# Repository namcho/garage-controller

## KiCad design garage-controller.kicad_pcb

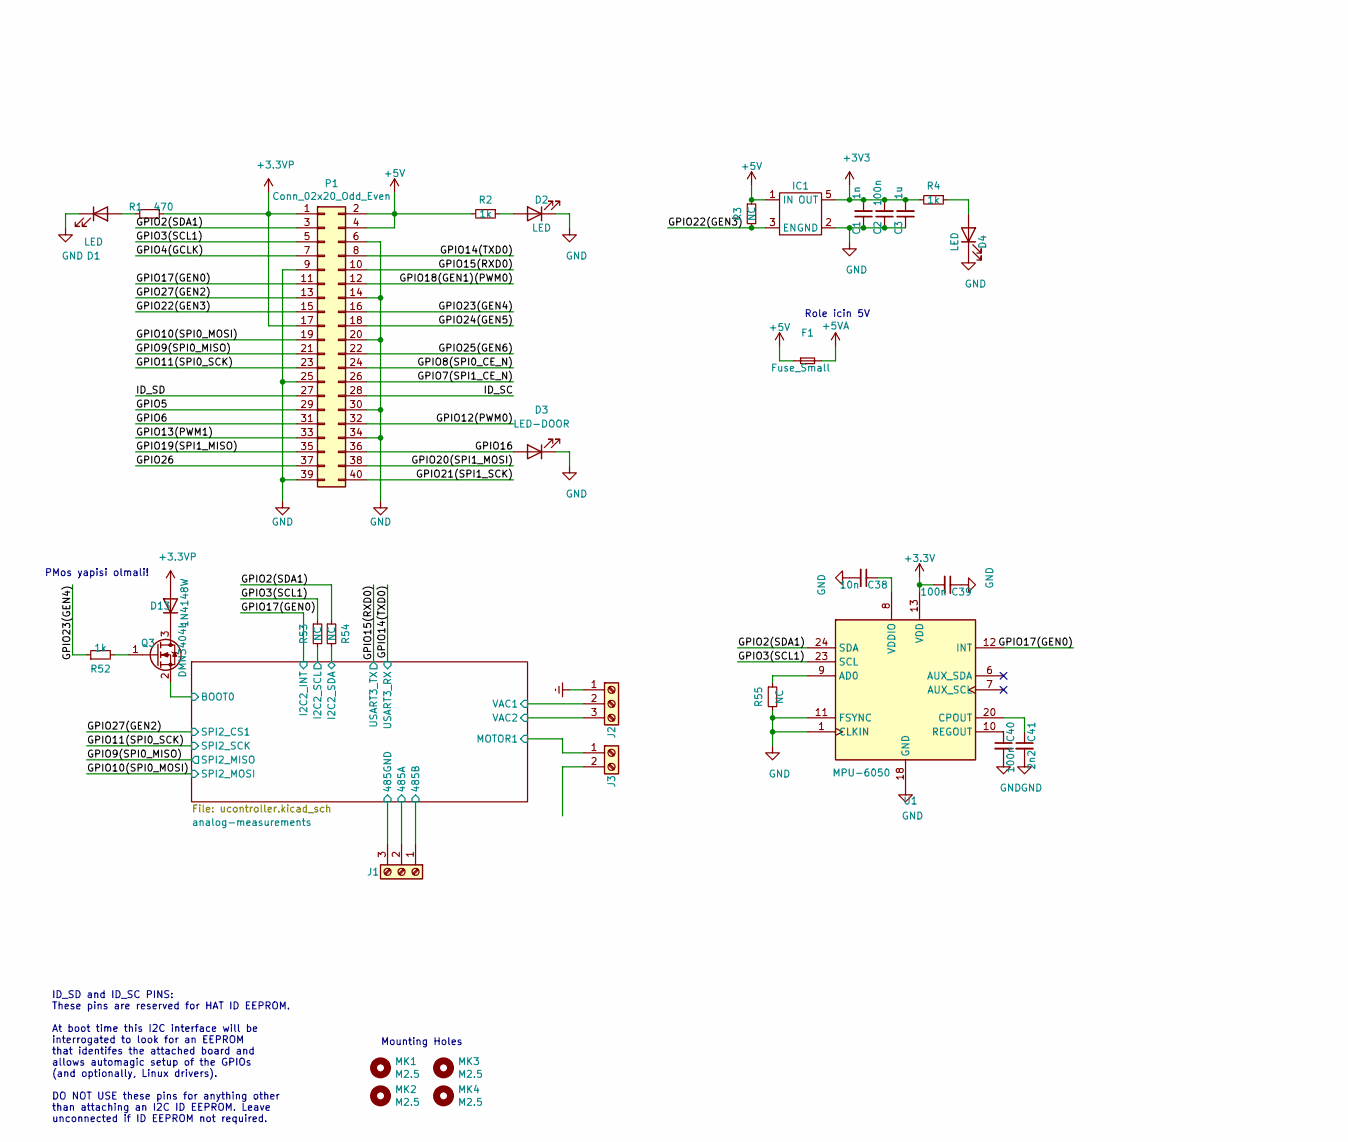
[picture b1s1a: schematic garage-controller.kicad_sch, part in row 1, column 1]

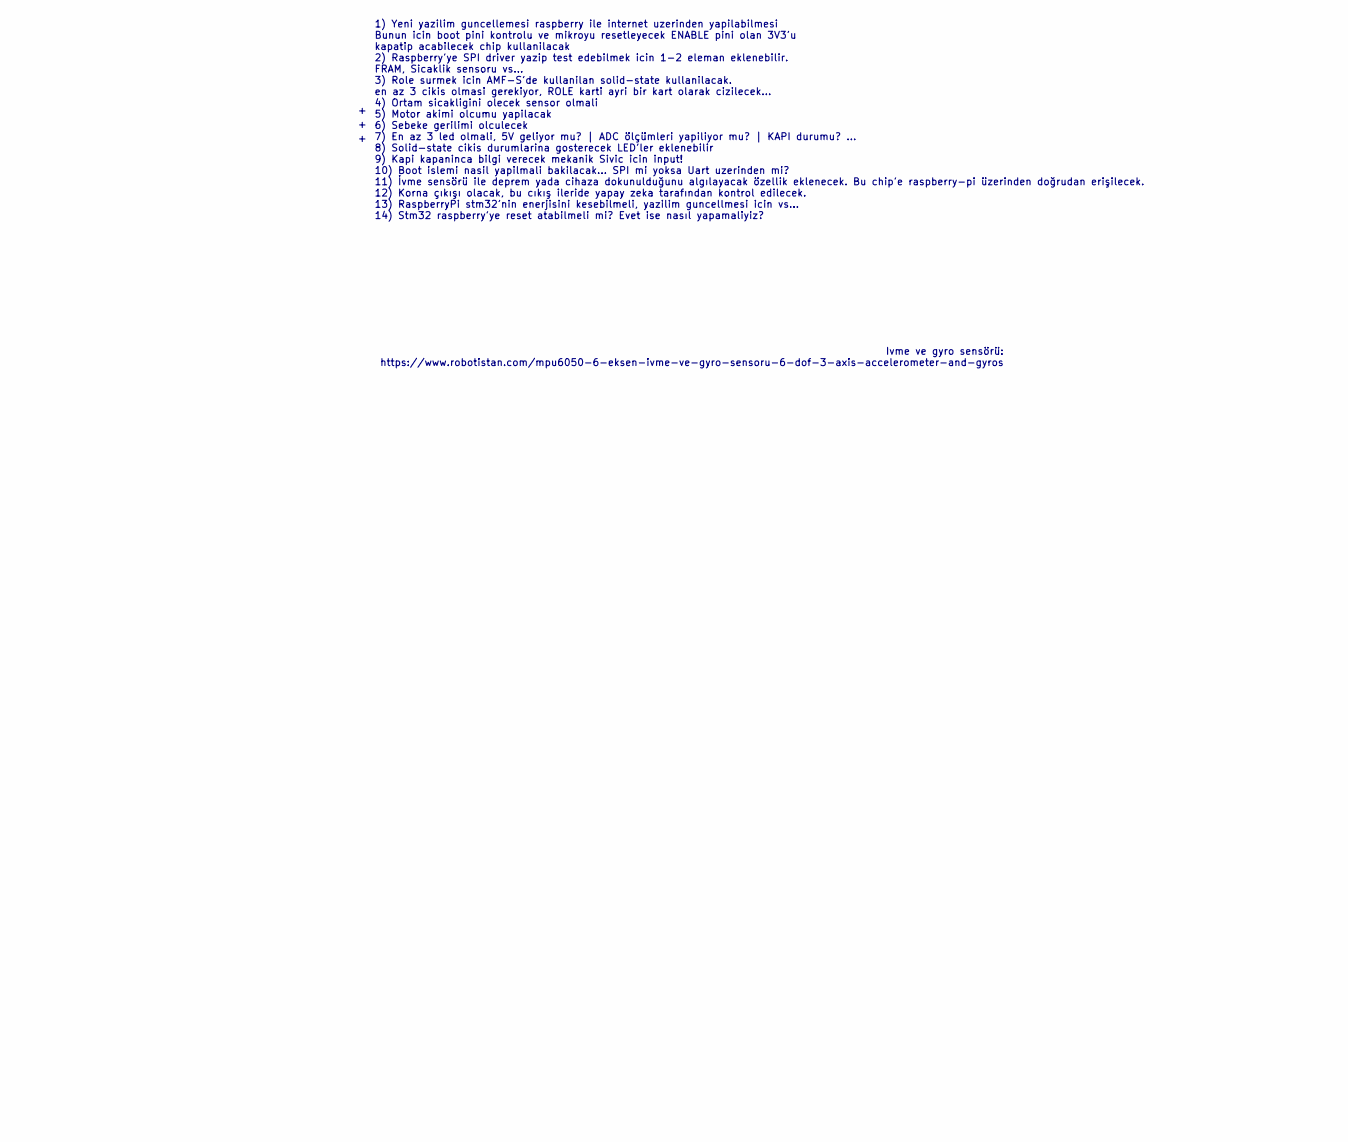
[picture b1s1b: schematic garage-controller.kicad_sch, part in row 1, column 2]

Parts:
C1: 1n; C_0603_1608Metric
C2, C39, C40: 100n; C_0603_1608Metric
C3: 1u; C_0603_1608Metric
C38: 10n; C_0603_1608Metric
C41: 2n2; C_0603_1608Metric
D1, D2, D4: LED; LED_0805_2012Metric
D3: LED-DOOR; LED_0805_2012Metric
D13: 1N4148W; D_SOD-123
F1: Fuse_Small; Fuse_1206_3216Metric
IC1: NCP115ASN330T2G; TSOP-5_1.65x3.05mm_P0.95mm
J1: Screw_Terminal_01x03; PhoenixContact_MCV_1,5_3-G-3.81_1x03_P3.81mm_Vertical
J2: Screw_Terminal_01x03; PhoenixContact_MCV_1,5_3-G-5.08_1x03_P5.08mm_Vertical
J3: Screw_Terminal_01x02; PhoenixContact_MCV_1,5_2-G-5.08_1x02_P5.08mm_Vertical
MK1, MK2, MK3, MK4: M2.5; MountingHole_2.7mm_M2.5
P1: Conn_02x20_Odd_Even; PinSocket_2x20_P2.54mm_Vertical
Q3: DMN3404L; SOT-23
R1: 470; R_0603_1608Metric
R2, R4, R52: 1k; R_0603_1608Metric
R3, R53, R54, R55: NC; R_0603_1608Metric
U1: MPU-6050; InvenSense_QFN-24_4x4mm_P0.5mm

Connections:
+3.3VP: D13.2 (A), P1.1, P1.17, R1.1
+5V: F1.1, IC1.1 (IN), P1.2, P1.4, R2.2, R3.1; also elsewhere on the board
+5VA: F1.2; also elsewhere on the board
/GPIO2(SDA1): P1.3, R54.1, U1.24 (SDA)
/GPIO3(SCL1): P1.5, R53.1, U1.23 (SCL)
/GPIO4(GCLK): P1.7
/GPIO5: P1.29
/GPIO6: P1.31
/GPIO7(SPI1_CE_N): P1.26
/GPIO8(SPI0_CE_N): P1.24
/GPIO9(SPI0_MISO): P1.21; also elsewhere on the board
/GPIO10(SPI0_MOSI): P1.19; also elsewhere on the board
/GPIO11(SPI0_SCK): P1.23; also elsewhere on the board
/GPIO12(PWM0): P1.32
/GPIO13(PWM1): P1.33
/GPIO14(TXD0): P1.8; also elsewhere on the board
/GPIO15(RXD0): P1.10; also elsewhere on the board
/GPIO16: D3.2 (A), P1.36
/GPIO17(GEN0): P1.11, U1.12 (INT); also elsewhere on the board
/GPIO18(GEN1)(PWM0): P1.12
/GPIO19(SPI1_MISO): P1.35
/GPIO20(SPI1_MOSI): P1.38
/GPIO21(SPI1_SCK): P1.40
/GPIO22(GEN3): IC1.3 (EN), P1.15, R3.2
/GPIO23(GEN4): P1.16, R52.1
/GPIO24(GEN5): P1.18
/GPIO25(GEN6): P1.22
/GPIO26: P1.37
/GPIO27(GEN2): P1.13; also elsewhere on the board
/ID_SC: P1.28
/ID_SD: P1.27
/analog-measurements/485A: J1.2; also elsewhere on the board
/analog-measurements/485B: J1.1; also elsewhere on the board
/analog-measurements/485GND: J1.3; also elsewhere on the board
/analog-measurements/BOOT0: Q3.2 (S); also elsewhere on the board
/analog-measurements/I2C2_SCL: R53.2; also elsewhere on the board
/analog-measurements/I2C2_SDA: R54.2; also elsewhere on the board
/analog-measurements/MOTOR1: J3.1; also elsewhere on the board
/analog-measurements/VAC1: J2.2; also elsewhere on the board
/analog-measurements/VAC2: J2.3; also elsewhere on the board
Earth: J2.1; also elsewhere on the board
GND: C1.1, C2.1, C3.1, C38.2, C39.1, C40.2, C41.2, D1.1 (K), D2.1 (K), D3.1 (K), D4.1 (K), IC1.2 (GND), P1.6, P1.9, P1.14, P1.20, P1.25, P1.30, P1.34, P1.39, R55.2, U1.1 (CLKIN), U1.11 (FSYNC), U1.18 (GND); also elsewhere on the board
unnamed: C38.1, U1.8 (VDDIO)
unnamed: C40.1, U1.10 (REGOUT)
unnamed: C41.1, U1.20 (CPOUT)
unnamed: D1.2 (A), R1.2
unnamed: D2.2 (A), R2.1
unnamed: D4.2 (A), R4.1
unnamed: D13.1 (K), Q3.3 (D)
unnamed: Q3.1 (G), R52.2
unnamed: R55.1, U1.9 (AD0)

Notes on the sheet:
ID_SD and ID_SC PINS: These pins are reserved for HAT ID EEPROM. At boot time this I2C interface will be interrogated to look for an EEPROM that identifes the attached board and allows automagic setup of the GPIOs (and optionally, Linux drivers). DO NOT USE these pins for anything other than attach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
PMos yapisi olmali!
Mounting Holes
Role icin 5V
1) Yeni yazilim guncellemesi raspberry ile internet uzerinden yapilabilmesi Bunun icin boot pini kontrolu ve mikroyu resetleyecek ENABLE pini olan 3V3'u kapatip acabilecek chip kullanilacak 2) Raspberry'ye SPI driver yazip test edebilmek icin 1-2 eleman eklenebilir. FRAM, Sicaklik sensoru vs... 3) 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
Ivme ve gyro sensörü: https://www.robotistan.com/mpu6050-6-eksen-ivme-ve-gyro-sensoru-6-dof-3-axis-accelerometer-and-gyros

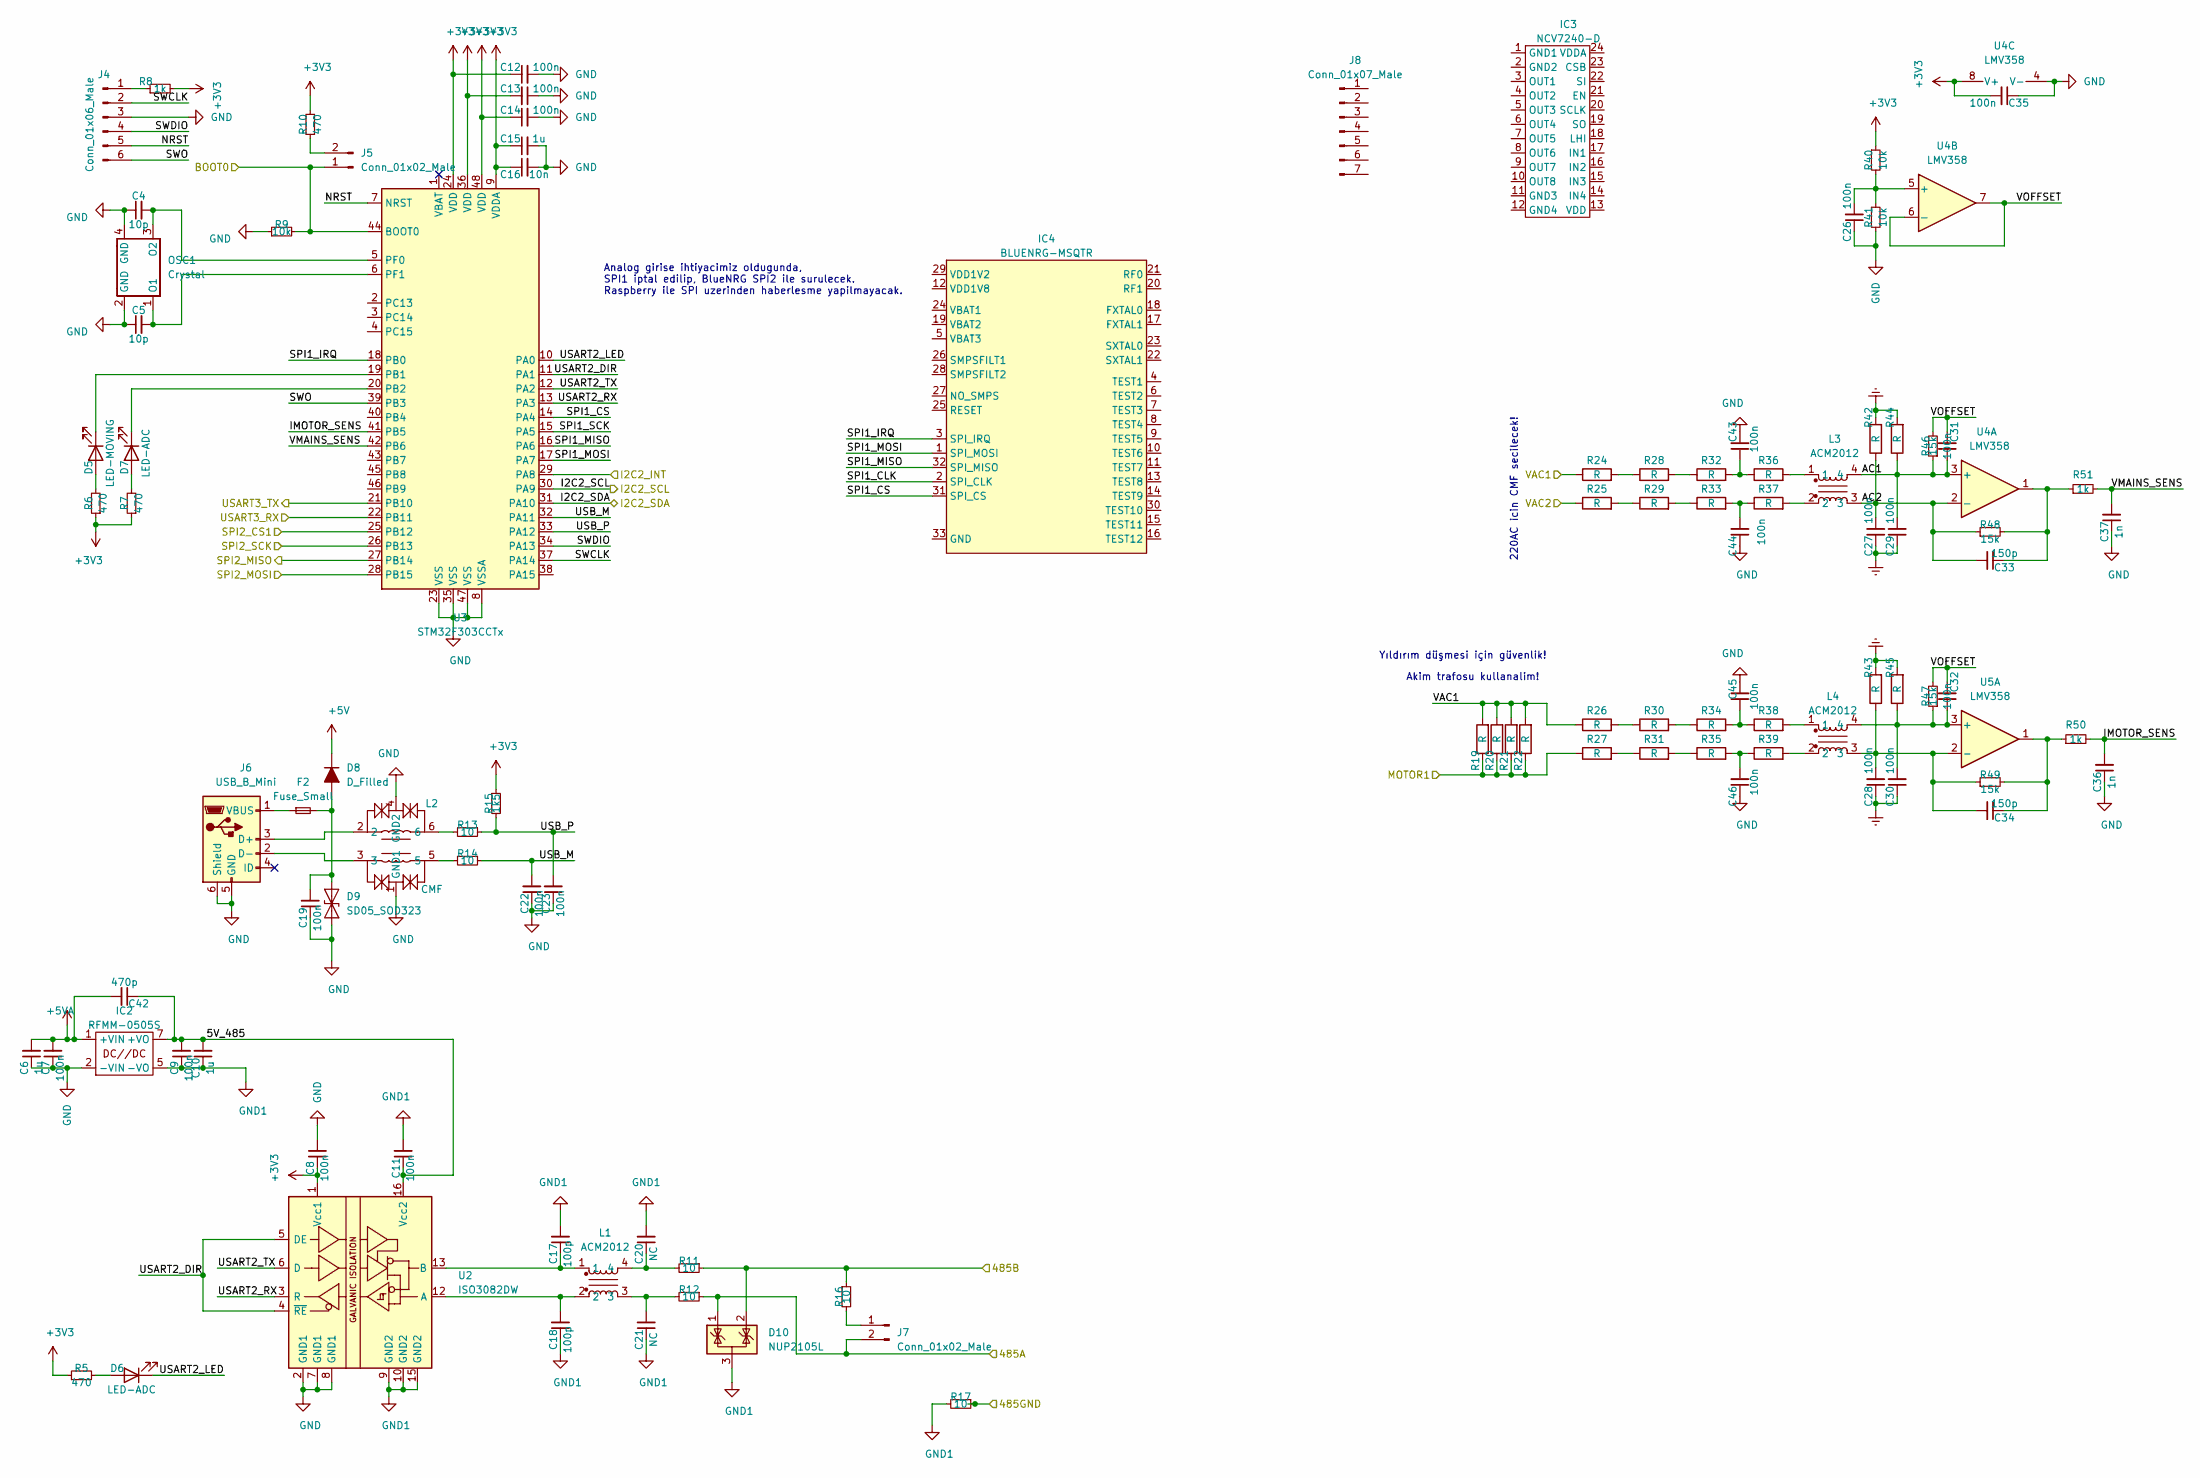
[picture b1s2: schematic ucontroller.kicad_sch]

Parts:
C4, C5: 10p; C_0603_1608Metric
C6, C10, C15: 1u; C_0603_1608Metric
C7, C8, C9, C11, C12, C13, C14, C19, C22, C23, C26, C27, C28, C29, C30, C31, C32, C35, C43, C44, C45, C46: 100n; C_0603_1608Metric
C16: 10n; C_0603_1608Metric
C17, C18: 100p; C_0603_1608Metric
C20, C21: NC; C_0603_1608Metric
C33, C34: 150p; C_0603_1608Metric
C36, C37: 1n; C_0603_1608Metric
C42: 470p; C_1206_3216Metric
D5: LED-MOVING; LED_0805_2012Metric
D6, D7: LED-ADC; LED_0805_2012Metric
D8: D_Filled; D_SOD-323
D9: SD05_SOD323; D_SOD-323
D10: NUP2105L; SOT-23
F2: Fuse_Small; Fuse_1206_3216Metric
IC2: RFMM-0505S; RFMM0505S
IC3: NCV7240-D; SOP65P600X175-24N
IC4: BLUENRG-MSQTR; STMicroelectronics-QFN32-0-0-0
J4: Conn_01x06_Male; PinHeader_1x06_P2.00mm_Vertical_SMD_Pin1Right
J5, J7: Conn_01x02_Male; PinHeader_1x02_P2.00mm_Vertical_SMD_Pin1Right
J6: USB_B_Mini; USB_Micro-B_Molex-105133-0001
J8: Conn_01x07_Male; PhoenixContact_MCV_1,5_7-G-3.81_1x07_P3.81mm_Vertical
L1, L3, L4: ACM2012; ACM2012_1
L2: CMF; EXC24CS900U
OSC1: Crystal; NX2016SA40MSTDCZS3
R5, R6, R7, R10: 470; R_0603_1608Metric
R8, R50, R51: 1k; R_0603_1608Metric
R9, R40, R41: 10k; R_0603_1608Metric
R11, R12, R13, R14, R16, R17: 10; R_0603_1608Metric
R15: 1k5; R_0603_1608Metric
R19, R20, R21, R22, R24, R25, R28, R29, R32, R33: R; R_1206_3216Metric
R26, R27, R30, R31, R34, R35, R36, R37, R38, R39, R42, R43, R44, R45: R; R_0603_1608Metric
R46, R47, R48, R49: 15k; R_0603_1608Metric
U2: ISO3082DW; SOIC-16W_7.5x10.3mm_P1.27mm
U3: STM32F303CCTx; LQFP-48_7x7mm_P0.5mm
U4: LMV358
U5: LMV358; MSOP-8_3x3mm_P0.65mm

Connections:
+5V: D8.1 (K); also elsewhere on the board
+5VA: C6.2, C7.2, C42.2, IC2.1 (+VIN); also elsewhere on the board
/GPIO9(SPI0_MISO): U3.27 (PB14); also elsewhere on the board
/GPIO10(SPI0_MOSI): U3.28 (PB15); also elsewhere on the board
/GPIO11(SPI0_SCK): U3.26 (PB13); also elsewhere on the board
/GPIO14(TXD0): U3.22 (PB11); also elsewhere on the board
/GPIO15(RXD0): U3.21 (PB10); also elsewhere on the board
/GPIO17(GEN0): U3.29 (PA8); also elsewhere on the board
/GPIO27(GEN2): U3.25 (PB12); also elsewhere on the board
/analog-measurements/5V_485: C9.2, C10.2, C11.1, C42.1, IC2.7 (+VO), U2.16 (Vcc2)
/analog-measurements/485A: D10.1 (K), J7.2, R12.1; also elsewhere on the board
/analog-measurements/485B: D10.2 (K), R11.1, R16.1; also elsewhere on the board
/analog-measurements/485GND: R17.1; also elsewhere on the board
/analog-measurements/AC1: C29.2, C31.1, L3.4, R44.1, R46.1, U4.3 (+)
/analog-measurements/AC2: C27.2, C33.2, L3.3, R42.1, R48.1, U4.2 (-)
/analog-measurements/BOOT0: J5.1, R9.2, U3.44 (BOOT0); also elsewhere on the board
/analog-measurements/I2C2_SCL: U3.30 (PA9); also elsewhere on the board
/analog-measurements/I2C2_SDA: U3.31 (PA10); also elsewhere on the board
/analog-measurements/IMOTOR_SENS: C36.2, R50.2, U3.41 (PB5)
/analog-measurements/MOTOR1: R19.1, R20.1, R21.1, R22.1, R27.1; also elsewhere on the board
/analog-measurements/NRST: J4.5, U3.7 (NRST)
/analog-measurements/SPI1_CLK: IC4.2 (SPI_CLK)
/analog-measurements/SPI1_CS: IC4.31 (SPI_CS), U3.14 (PA4)
/analog-measurements/SPI1_IRQ: IC4.3 (SPI_IRQ), U3.18 (PB0)
/analog-measurements/SPI1_MISO: IC4.32 (SPI_MISO), U3.16 (PA6)
/analog-measurements/SPI1_MOSI: IC4.1 (SPI_MOSI), U3.17 (PA7)
/analog-measurements/SPI1_SCK: U3.15 (PA5)
/analog-measurements/SWCLK: J4.2, U3.37 (PA14)
/analog-measurements/SWDIO: J4.4, U3.34 (PA13)
/analog-measurements/SWO: J4.6, U3.39 (PB3)
/analog-measurements/USART2_DIR: U2.4 (~RE), U2.5 (DE), U3.11 (PA1)
/analog-measurements/USART2_LED: D6.1 (K), U3.10 (PA0)
/analog-measurements/USART2_RX: U2.3 (R), U3.13 (PA3)
/analog-measurements/USART2_TX: U2.6 (D), U3.12 (PA2)
/analog-measurements/USB_M: C22.2, R14.1, U3.32 (PA11)
/analog-measurements/USB_P: C23.2, R13.1, R15.2, U3.33 (PA12)
/analog-measurements/VAC1: R19.2, R20.2, R21.2, R22.2, R24.1, R26.1; also elsewhere on the board
/analog-measurements/VAC2: R25.1; also elsewhere on the board
/analog-measurements/VMAINS_SENS: C37.2, R51.2, U3.42 (PB6)
/analog-measurements/VOFFSET: C31.2, C32.2, R46.2, R47.2, U4.6 (-), U4.7
Earth: C27.1, C28.1, C29.1, C30.1, R42.2, R43.2, R44.2, R45.2; also elsewhere on the board
GND: C4.1, C5.1, C6.1, C7.1, C8.2, C12.2, C13.1, C14.2, C15.2, C16.2, C19.1, C22.1, C23.1, C26.1, C35.1, C36.1, C37.1, C43.2, C44.1, C45.2, C46.1, D9.1 (A1), IC2.2 (-VIN), J4.3, J6.5 (GND), J6.6 (Shield), L2.1 (GND1), L2.4 (GND2), OSC1.2 (GND), OSC1.4 (GND), R9.1, R41.2, U2.2 (GND1), U2.7 (GND1), U2.8 (GND1), U3.8 (VSSA), U3.23 (VSS), U3.35 (VSS), U3.47 (VSS), U4.4 (V-); also elsewhere on the board
GND1: C9.1, C10.1, C11.2, C17.2, C18.1, C20.2, C21.1, D10.3 (A), IC2.5 (-VO), R17.2, U2.9 (GND2), U2.10 (GND2), U2.15 (GND2)
unnamed: C4.2, OSC1.3 (O2), U3.5 (PF0)
unnamed: C5.2, OSC1.1 (O1), U3.6 (PF1)
unnamed: C17.1, L1.1, U2.13 (B)
unnamed: C18.2, L1.2, U2.12 (A)
unnamed: C19.2, D8.2 (A), D9.2 (A2), F2.2
unnamed: C20.1, L1.4, R11.2
unnamed: C21.2, L1.3, R12.2
unnamed: C26.2, R40.2, R41.1, U4.5 (+)
unnamed: C28.2, C34.2, L4.3, R43.1, R49.1, U5.2 (-)
unnamed: C30.2, C32.1, L4.4, R45.1, R47.1, U5.3 (+)
unnamed: C33.1, R48.2, R51.1, U4.1
unnamed: C34.1, R49.2, R50.1, U5.1
unnamed: C43.1, R32.2, R36.1
unnamed: C44.2, R33.2, R37.1
unnamed: C45.1, R34.2, R38.1
unnamed: C46.2, R35.2, R39.1
unnamed: D5.2 (A), R6.2
unnamed: D6.2 (A), R5.2
unnamed: D7.2 (A), R7.2
unnamed: F2.1, J6.1 (VBUS)
unnamed: J4.1, R8.1
unnamed: J5.2, R10.1
unnamed: J6.2 (D-), L2.3
unnamed: J6.3 (D+), L2.2
unnamed: J7.1, R16.2
unnamed: L2.5, R14.2
unnamed: L2.6, R13.2
unnamed: L3.1, R36.2
unnamed: L3.2, R37.2
unnamed: L4.1, R38.2
unnamed: L4.2, R39.2
unnamed: R24.2, R28.1
unnamed: R25.2, R29.1
unnamed: R26.2, R30.1
unnamed: R27.2, R31.1
unnamed: R28.2, R32.1
unnamed: R29.2, R33.1
unnamed: R30.2, R34.1
unnamed: R31.2, R35.1
unnamed: D5.1 (K), U3.19 (PB1)
unnamed: D7.1 (K), U3.20 (PB2)

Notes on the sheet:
Analog girise ihtiyacimiz oldugunda, SPI1 iptal edilip, BlueNRG SPI2 ile surulecek. Raspberry ile SPI uzerinden haberlesme yapilmayacak.
220AC icin CMF secilecek!
Akim trafosu kullanalim!
Yıldırım düşmesi için güvenlik!

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
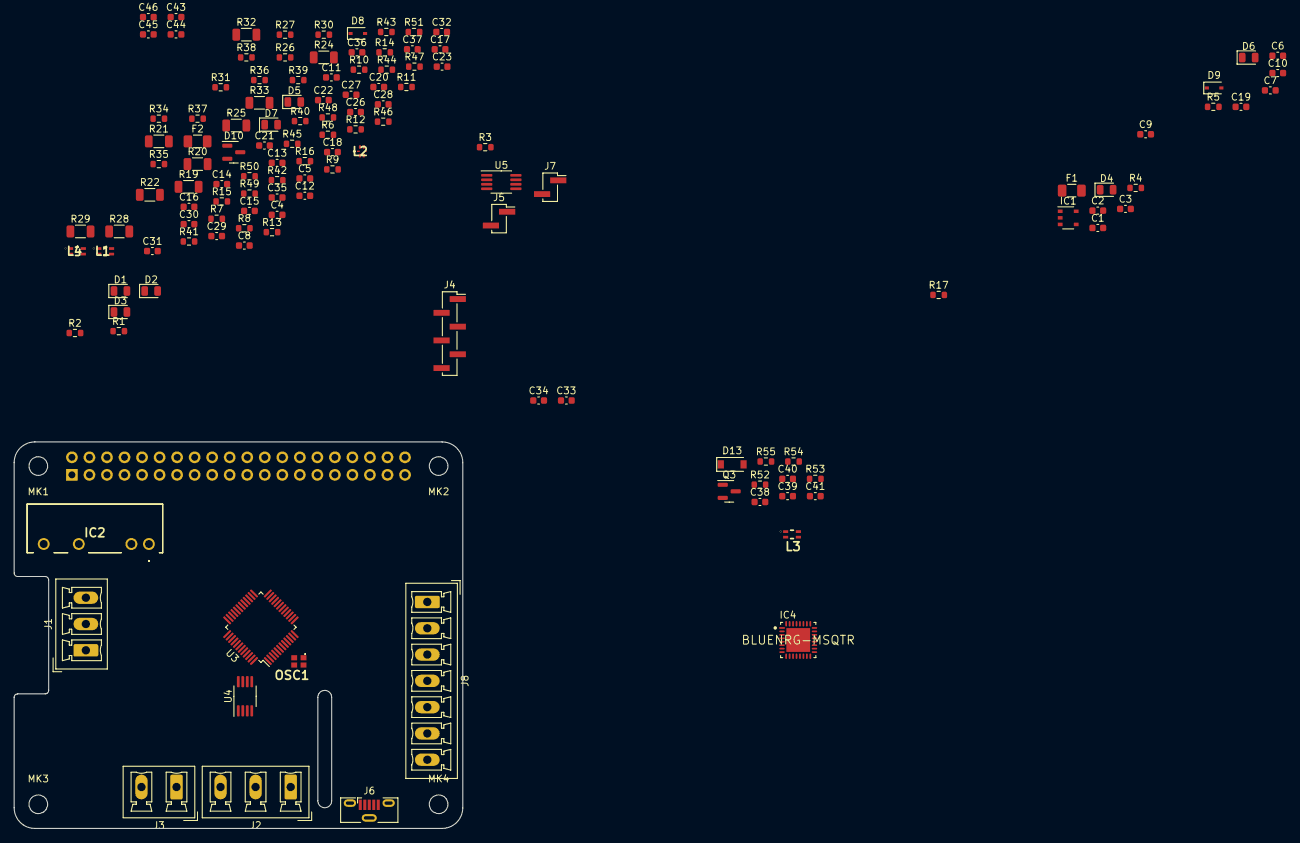
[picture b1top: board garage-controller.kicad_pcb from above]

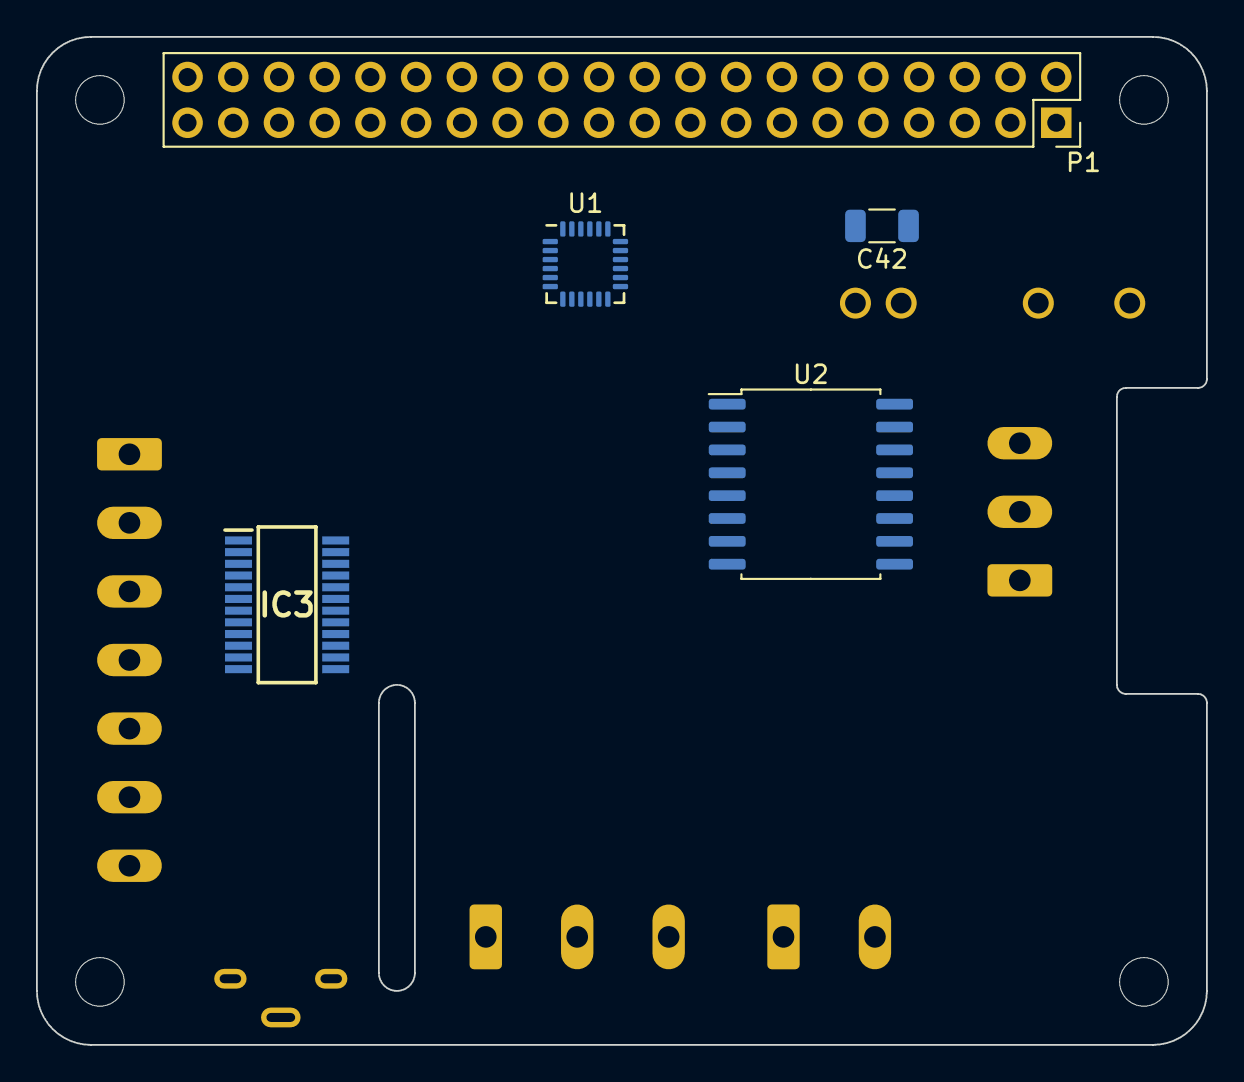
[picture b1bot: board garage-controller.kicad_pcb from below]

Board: 4 copper layers, 65.0 x 56.0 mm, 138 parts (5 on the bottom side), 98 nets.
